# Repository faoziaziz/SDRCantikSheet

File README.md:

Ini adalah dokument TA tentang pembuatan SDR Cantik

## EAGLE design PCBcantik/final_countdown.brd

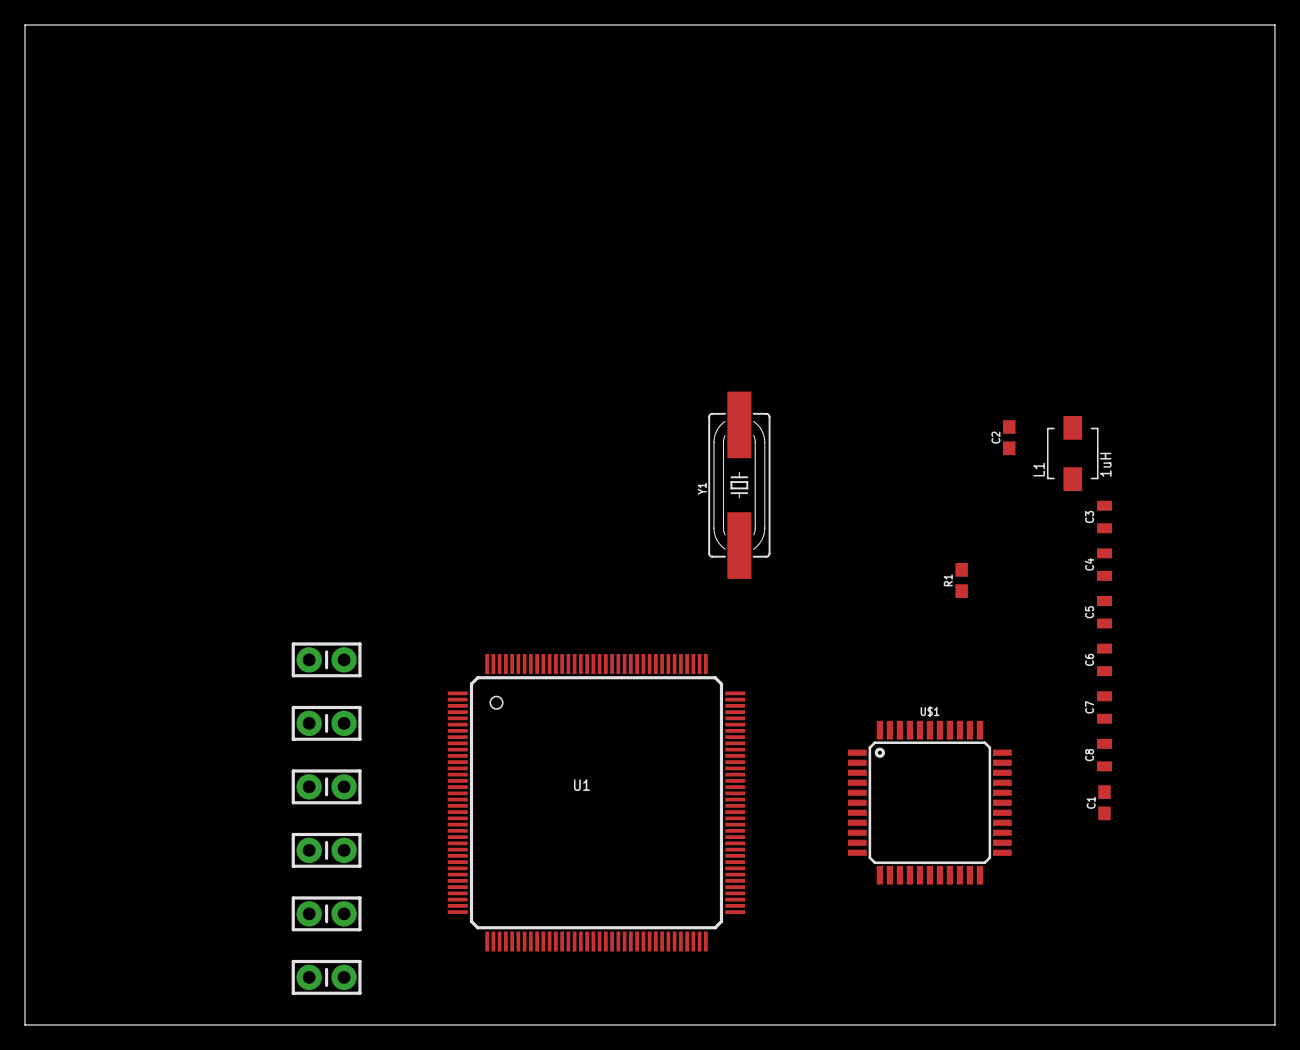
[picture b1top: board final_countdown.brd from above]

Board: 2 copper layers, 100.0 x 80.0 mm, 19 parts (0 on the bottom side), 6 nets, no tracks yet.

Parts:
C1, C2: 22pF; 0603
C3, C4, C5, C6, C7, C8: 1.0uF; 0805
C9, C10, C11, C12, C13, C14: 0.1uF; CAP-PTH-SMALL-KIT
L1: 1uH; INDUCTOR-SRP4020
R1: 10k; 0603
U1: 6SLX9TQG144; TQ144
U$1: 32U4; TQFP44
Y1: 8MHz; HC49UP

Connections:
3.3V: C5.1, C6.1, C8.1, C9.1, C10.1, C11.1, C12.1, C13.1, C14.1, L1.P$1, R1.2, U1.P20, U1.P36, U1.P53, U1.P90, U1.P122, U1.P125, U1.P129, U1.P135, U$1.6, U$1.14, U$1.34
GND: C1.2, C2.2, C3.2, C4.2, C5.2, C6.2, C8.2, C9.2, C10.2, C11.2, C12.2, C13.2, C14.2, U1.P3, U1.P13, U1.P25, U1.P49, U1.P54, U1.P68, U1.P77, U1.P91, U1.P96, U1.P108, U1.P113, U1.P130, U1.P136, U$1.5, U$1.15, U$1.23, U$1.33, U$1.35, U$1.43
unnamed: C2.1, U$1.16, Y1.1
unnamed: C1.1, U$1.17, Y1.2
unnamed: C3.1, L1.P$2
unnamed: R1.1, U$1.13

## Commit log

2018-01-27 Aziz memang gege

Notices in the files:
parts and their libraries:
SparkFun-Capacitors: Licensing: Creative Commons ShareAlike 4.0 International - https://creativecommons.org/licenses/by-sa/4.0
